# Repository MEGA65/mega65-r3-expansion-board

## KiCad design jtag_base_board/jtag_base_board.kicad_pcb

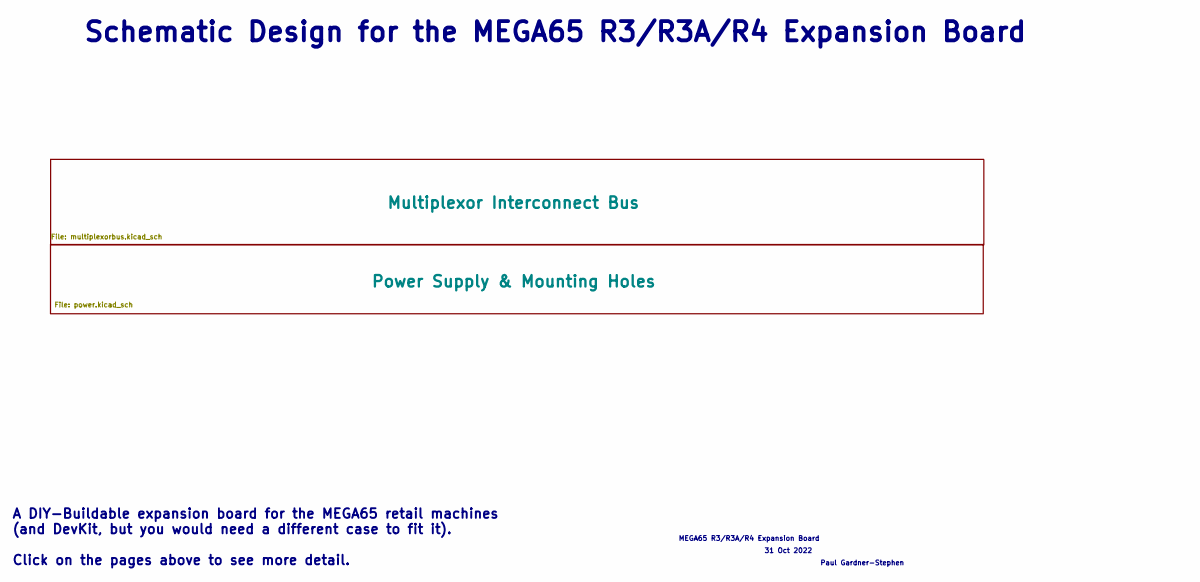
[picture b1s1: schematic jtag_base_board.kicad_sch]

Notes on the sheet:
Paul Gardner-Stephen
A DIY-Buildable expansion board for the MEGA65 retail machines (and DevKit, but you would need a different case to fit it). Click on the pages above to see more detail.
31 Oct 2022
MEGA65 R3/R3A/R4 Expansion Board
Schematic Design for the MEGA65 R3/R3A/R4 Expansion Board

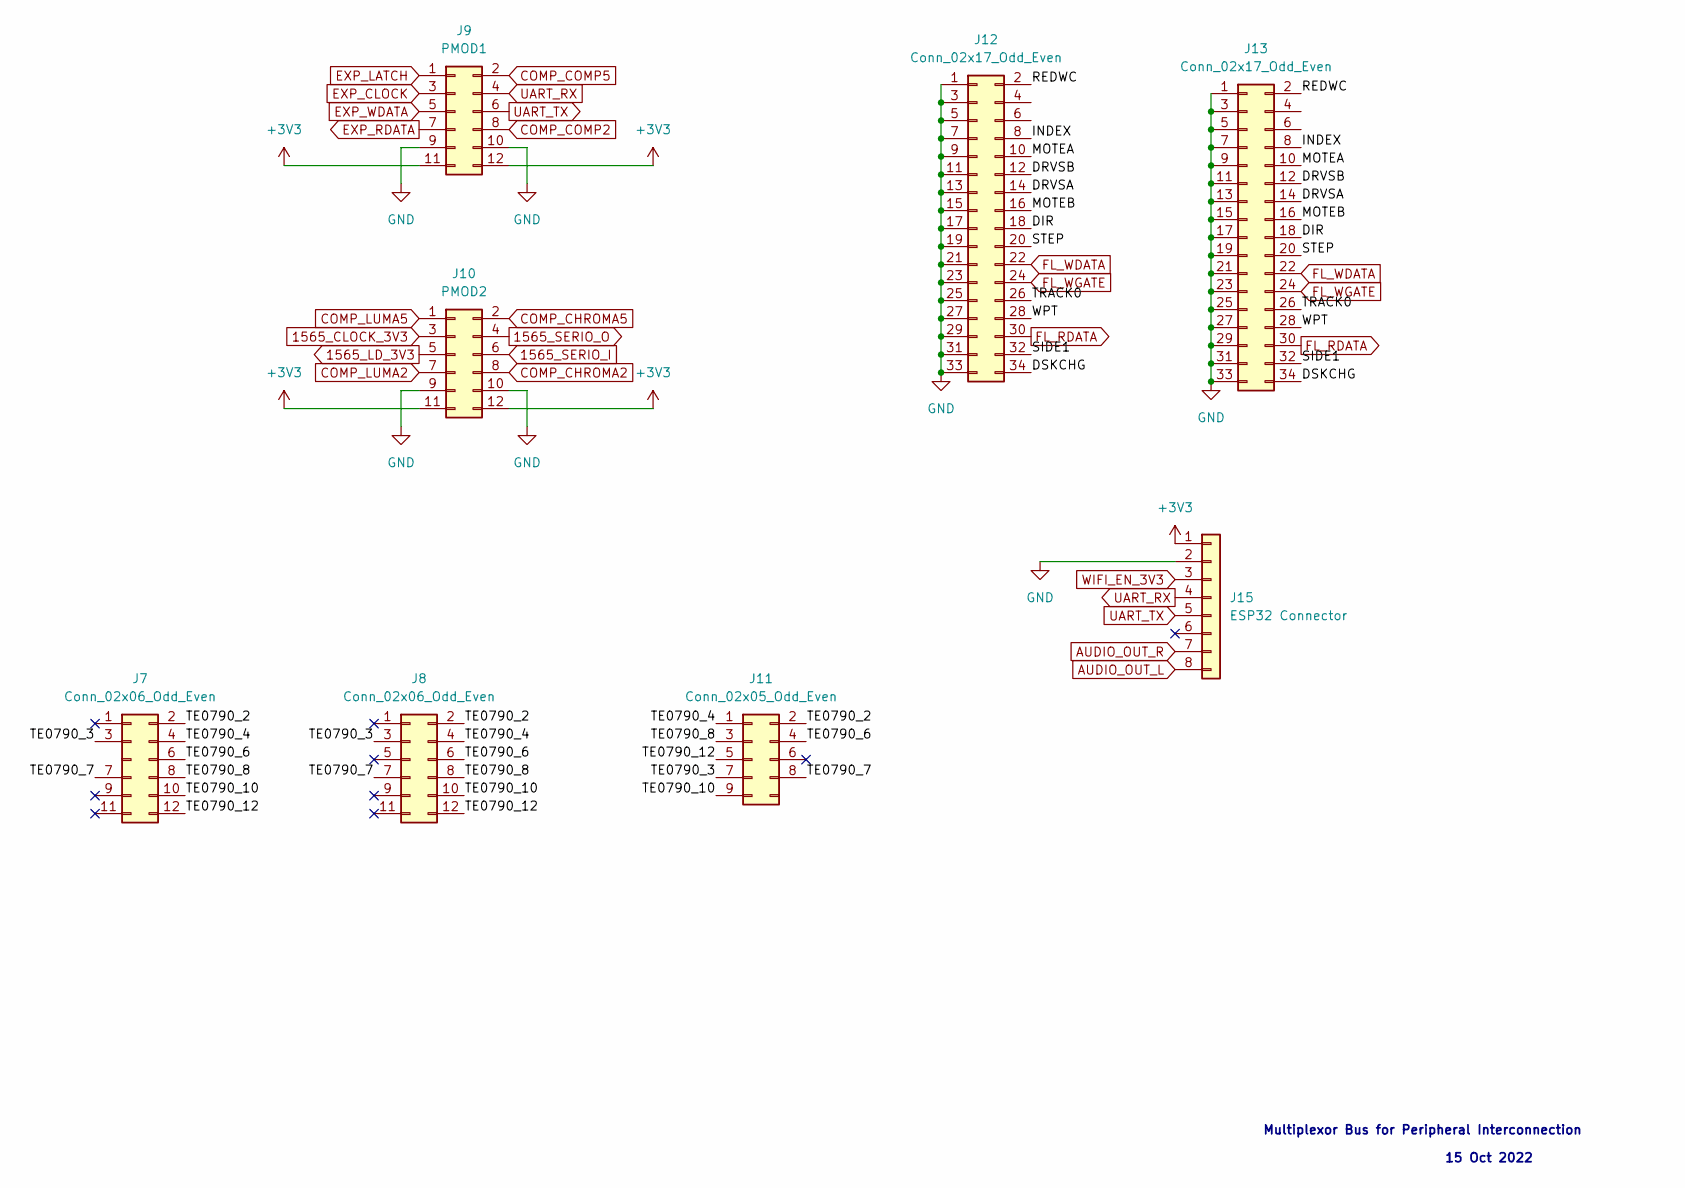
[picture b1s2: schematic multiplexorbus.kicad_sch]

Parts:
J7, J8: Conn_02x06_Odd_Even; PinHeader_2x06_P2.54mm_Vertical
J9: PMOD1; PinHeader_2x06_P2.54mm_Vertical
J10: PMOD2; PinHeader_2x06_P2.54mm_Vertical
J11: Conn_02x05_Odd_Even; PinHeader_2x05_P2.54mm_Vertical
J12, J13: Conn_02x17_Odd_Even; PinHeader_2x17_P2.54mm_Vertical
J15: ESP32 Connector; PinHeader_1x08_P2.54mm_Vertical

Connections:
1565_CLOCK_3V3: J10.3
1565_LD_3V3: J10.5
1565_SERIO_I: J10.6
1565_SERIO_O: J10.4
+3V3: J9.11, J9.12, J10.11, J10.12, J15.1
/Multiplexor Interconnect Bus/DIR: J12.18, J13.18
/Multiplexor Interconnect Bus/DRVSA: J12.14, J13.14
/Multiplexor Interconnect Bus/DRVSB: J12.12, J13.12
/Multiplexor Interconnect Bus/DSKCHG: J12.34, J13.34
/Multiplexor Interconnect Bus/INDEX: J12.8, J13.8
/Multiplexor Interconnect Bus/MOTEA: J12.10, J13.10
/Multiplexor Interconnect Bus/MOTEB: J12.16, J13.16
/Multiplexor Interconnect Bus/REDWC: J12.2, J13.2
/Multiplexor Interconnect Bus/SIDE1: J12.32, J13.32
/Multiplexor Interconnect Bus/STEP: J12.20, J13.20
/Multiplexor Interconnect Bus/TE0790_2: J7.2, J8.2, J11.2
/Multiplexor Interconnect Bus/TE0790_3: J7.3, J8.3, J11.7
/Multiplexor Interconnect Bus/TE0790_4: J7.4, J8.4, J11.1
/Multiplexor Interconnect Bus/TE0790_6: J7.6, J8.6, J11.4
/Multiplexor Interconnect Bus/TE0790_7: J7.7, J8.7, J11.8
/Multiplexor Interconnect Bus/TE0790_8: J7.8, J8.8, J11.3
/Multiplexor Interconnect Bus/TE0790_10: J7.10, J8.10, J11.9
/Multiplexor Interconnect Bus/TE0790_12: J7.12, J8.12, J11.5
/Multiplexor Interconnect Bus/TRACK0: J12.26, J13.26
/Multiplexor Interconnect Bus/WPT: J12.28, J13.28
AUDIO_OUT_L: J15.8
AUDIO_OUT_R: J15.7
COMP_CHROMA2: J10.8
COMP_CHROMA5: J10.2
COMP_COMP2: J9.8
COMP_COMP5: J9.2
COMP_LUMA2: J10.7
COMP_LUMA5: J10.1
EXP_CLOCK: J9.3
EXP_LATCH: J9.1
EXP_RDATA: J9.7
EXP_WDATA: J9.5
FL_RDATA: J12.30, J13.30
FL_WDATA: J12.22, J13.22
FL_WGATE: J12.24, J13.24
GND: J9.9, J9.10, J10.9, J10.10, J12.1, J12.3, J12.5, J12.7, J12.9, J12.11, J12.13, J12.15, J12.17, J12.19, J12.21, J12.23, J12.25, J12.27, J12.29, J12.31, J12.33, J13.1, J13.3, J13.5, J13.7, J13.9, J13.11, J13.13, J13.15, J13.17, J13.19, J13.21, J13.23, J13.25, J13.27, J13.29, J13.31, J13.33, J15.2; also elsewhere on the board
UART_RX: J9.4, J15.4
UART_TX: J9.6, J15.5
WIFI_EN_3V3: J15.3

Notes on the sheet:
Multiplexor Bus for Peripheral Interconnection
15 Oct 2022

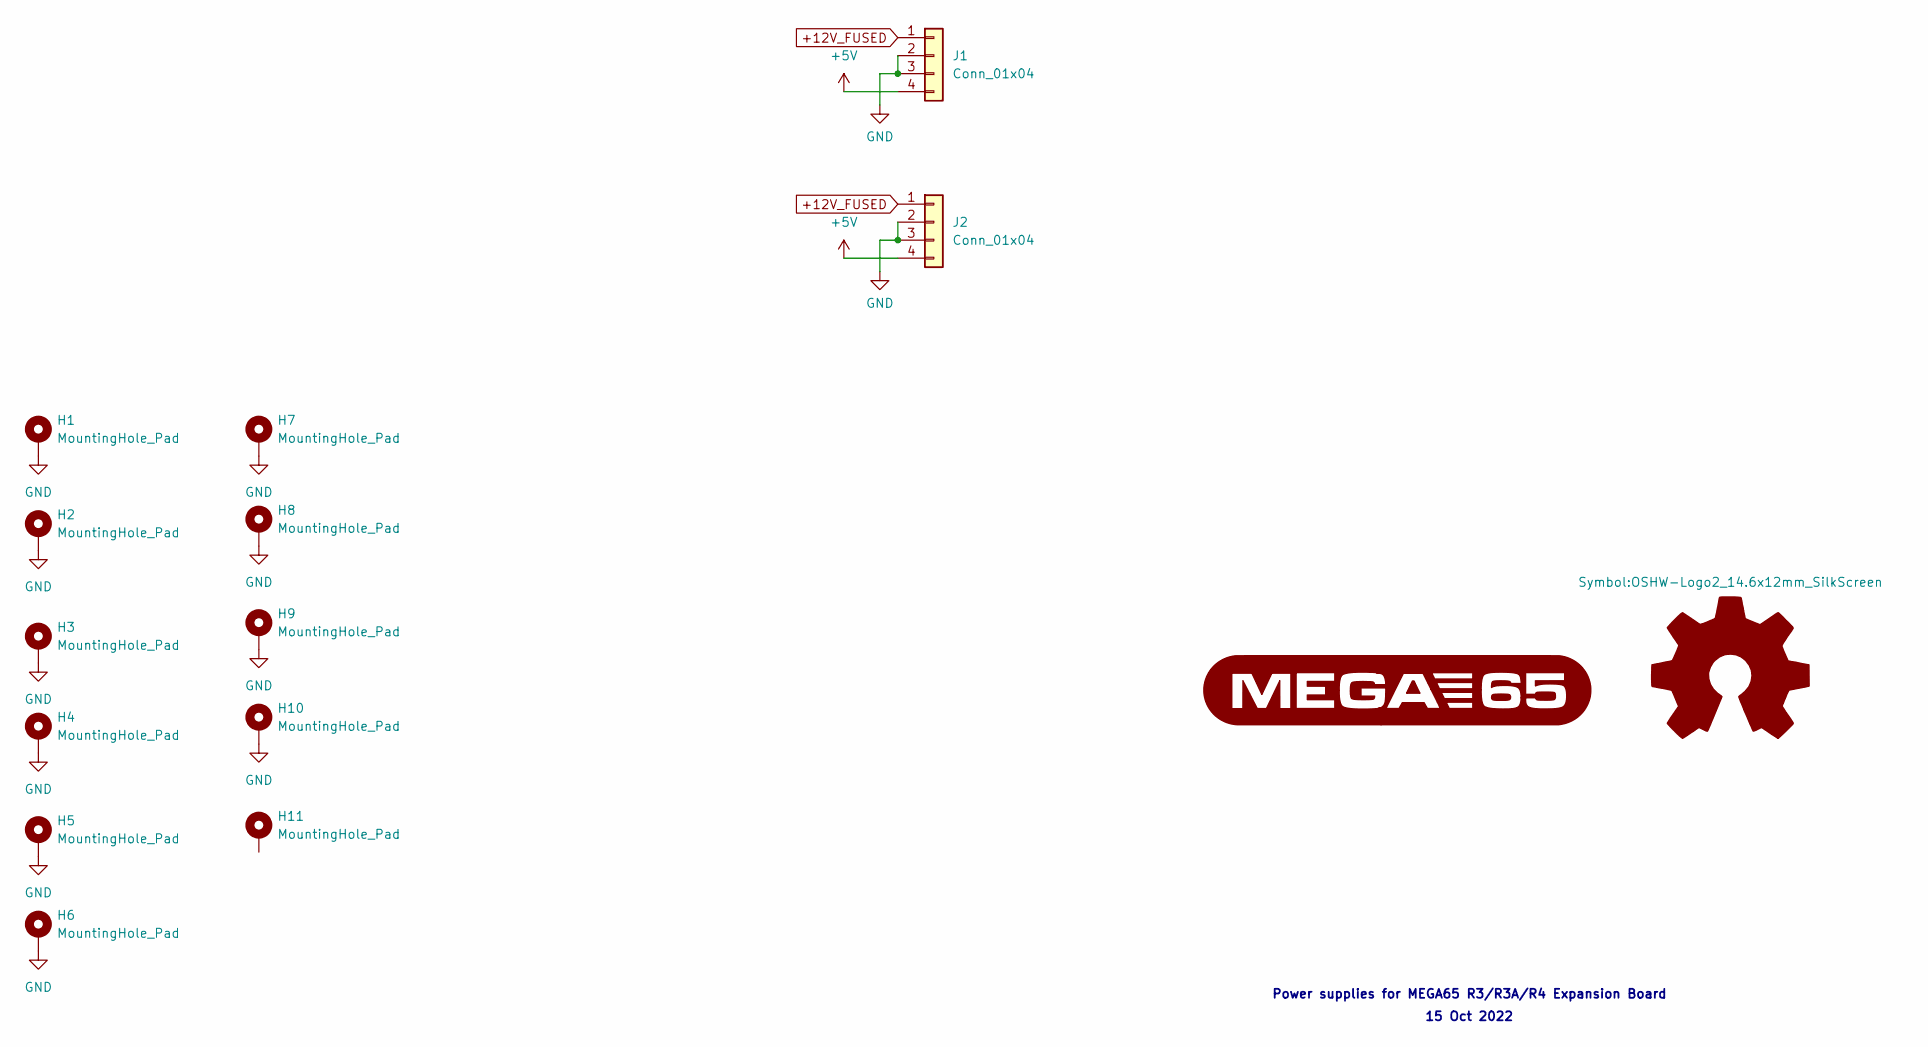
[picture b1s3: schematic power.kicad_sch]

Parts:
H1, H2, H3, H4, H5, H6, H7, H8, H9, H10, H11: MountingHole_Pad; MountingHole_3.2mm_M3_DIN965_Pad
J1, J2: Conn_01x04; FloppyPower
LOGO1: Logo_Open_Hardware_Large; OSHW-Logo2_14.6x12mm_SilkScreen

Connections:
+5V: J1.4, J2.4
+12V_FUSED: J1.1, J2.1
GND: H1.1 (1_1), H2.1 (1_1), H3.1 (1_1), H4.1 (1_1), H5.1 (1_1), H6.1 (1_1), H7.1 (1_1), H8.1 (1_1), H9.1 (1_1), H10.1 (1_1), J1.2, J1.3, J2.2, J2.3; also elsewhere on the board

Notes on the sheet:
Power supplies for MEGA65 R3/R3A/R4 Expansion Board
15 Oct 2022

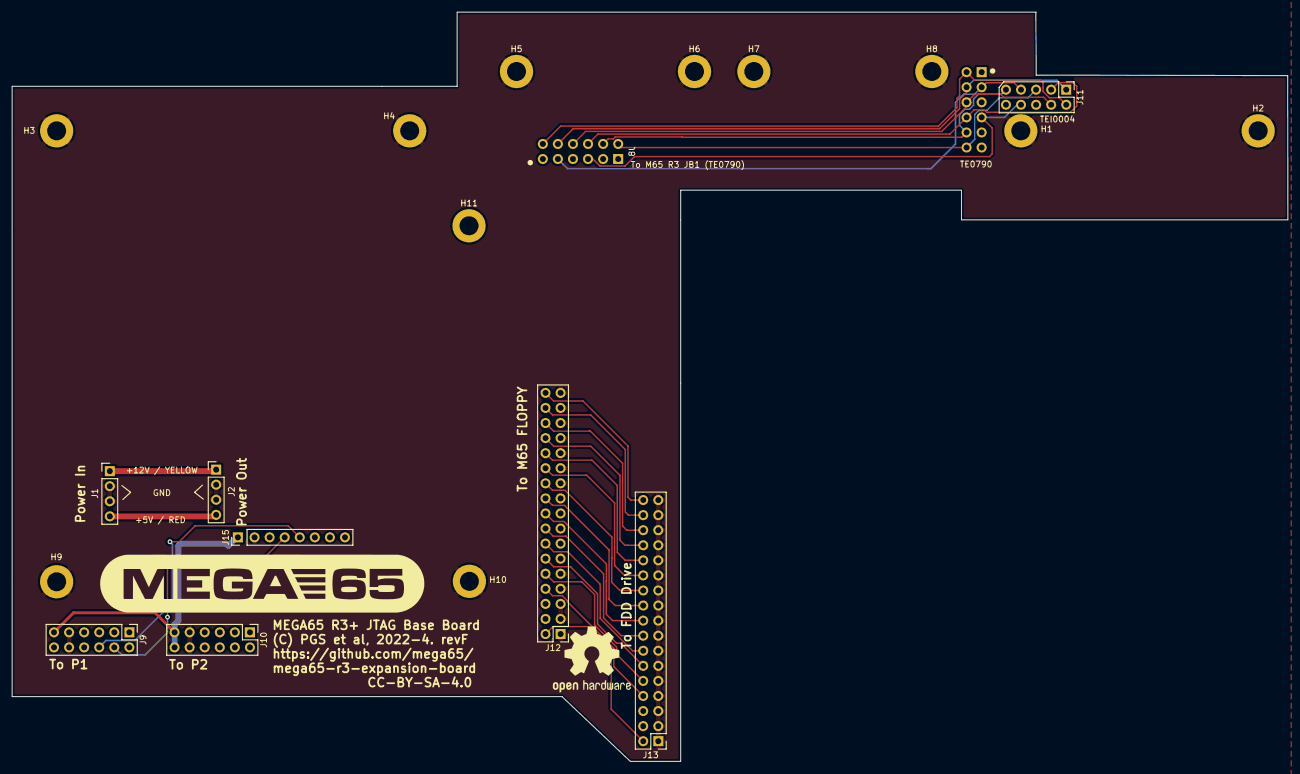
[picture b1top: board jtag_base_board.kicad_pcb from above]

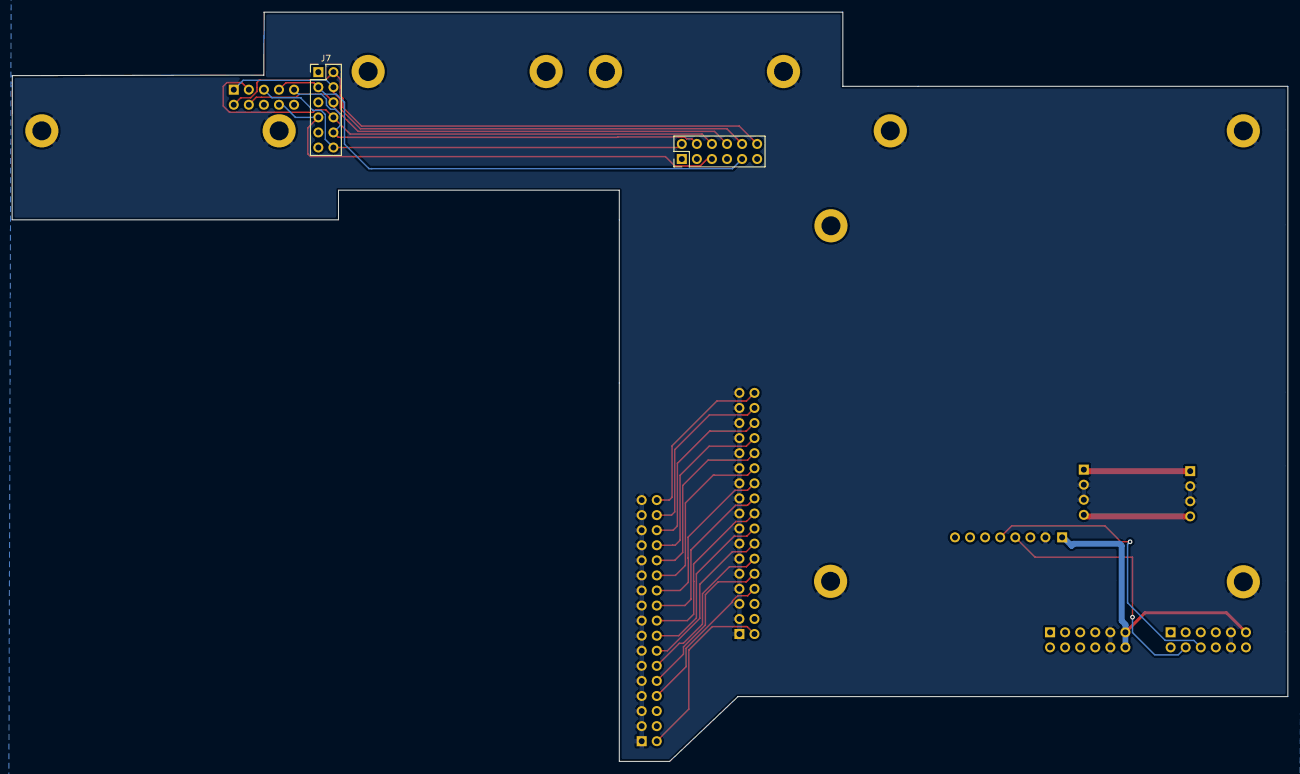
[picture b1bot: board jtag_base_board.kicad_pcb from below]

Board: 2 copper layers, 215.0 x 126.3 mm, 22 parts (2 on the bottom side), 29 nets.

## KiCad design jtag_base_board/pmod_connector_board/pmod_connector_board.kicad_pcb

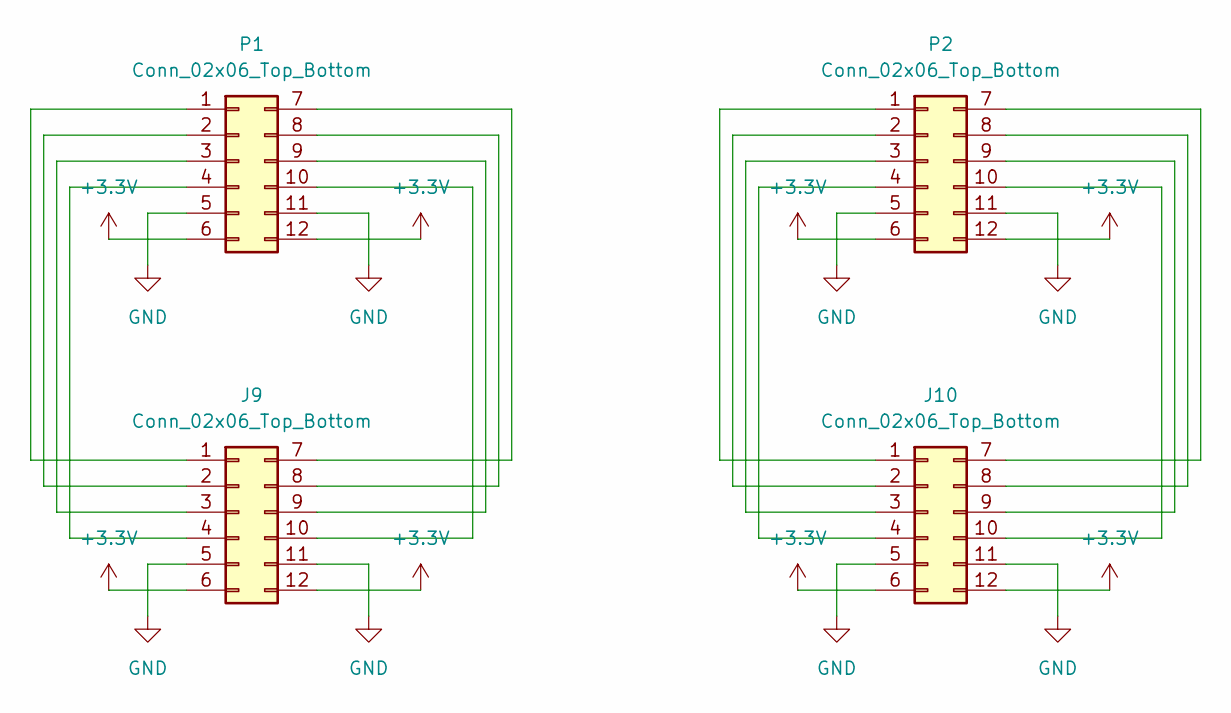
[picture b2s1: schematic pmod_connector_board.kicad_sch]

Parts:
J9, J10: Conn_02x06_Top_Bottom; PinHeader_2x06_P1.00mm_Vertical
P1, P2: Conn_02x06_Top_Bottom; PinHeader_2x06_P1.00mm_Vertical

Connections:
+3V3: J9.6, J9.12, J10.6, J10.12, P1.6, P1.12, P2.6, P2.12
GND: J9.5, J9.11, J10.5, J10.11, P1.5, P1.11, P2.5, P2.11
unnamed: J9.1, P1.1
unnamed: J9.2, P1.2
unnamed: J9.3, P1.3
unnamed: J9.4, P1.4
unnamed: J9.7, P1.7
unnamed: J9.8, P1.8
unnamed: J9.9, P1.9
unnamed: J9.10, P1.10
unnamed: J10.1, P2.1
unnamed: J10.2, P2.2
unnamed: J10.3, P2.3
unnamed: J10.4, P2.4
unnamed: J10.7, P2.7
unnamed: J10.8, P2.8
unnamed: J10.9, P2.9
unnamed: J10.10, P2.10

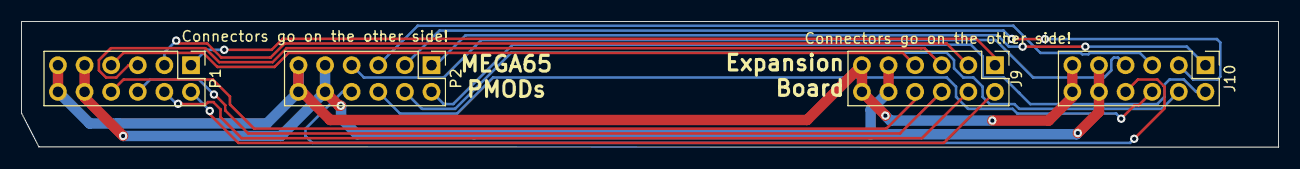
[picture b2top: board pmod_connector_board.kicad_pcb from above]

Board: 2 copper layers, 120.0 x 12.0 mm, 4 parts (0 on the bottom side), 18 nets.

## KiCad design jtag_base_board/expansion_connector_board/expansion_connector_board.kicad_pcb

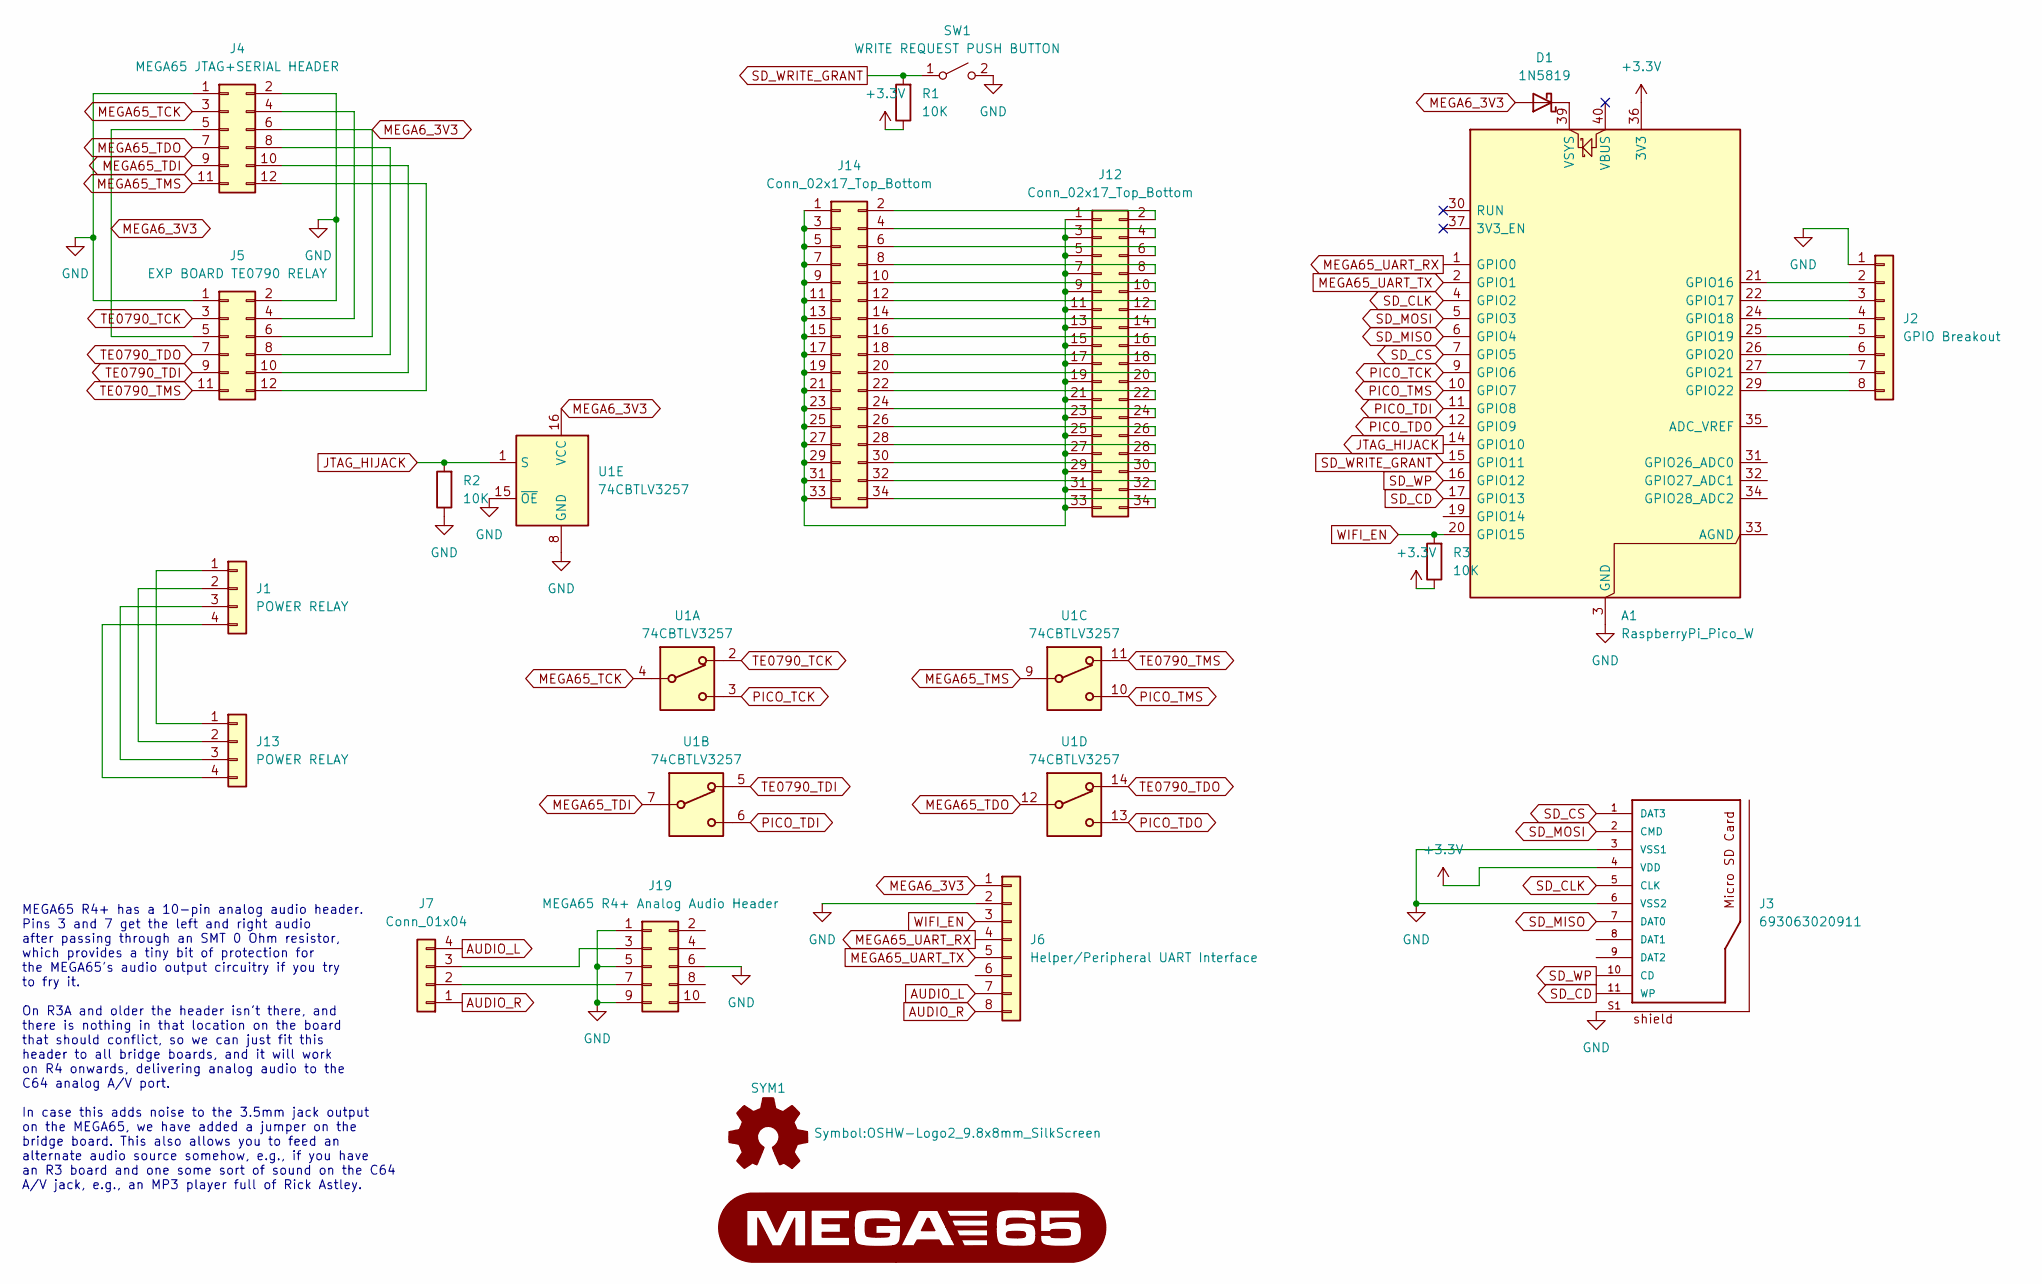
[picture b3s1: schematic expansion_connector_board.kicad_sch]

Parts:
A1: RaspberryPi_Pico_W; RaspberryPi_Pico_W_SMD_HandSolder
D1: 1N5819; D_DO-41_SOD81_P10.16mm_Horizontal
G1: LOGO; MEGA65-logo
J1, J13: POWER RELAY; PinHeader_1x04_P2.54mm_Vertical
J2: GPIO Breakout; PinHeader_1x08_P2.54mm_Vertical
J3: 693063020911
J4: MEGA65 JTAG+SERIAL HEADER; PinHeader_2x06_P2.54mm_Vertical
J5: EXP BOARD TE0790 RELAY; PinHeader_2x06_P2.54mm_Vertical
J6: Helper/Peripheral UART Interface; PinHeader_1x08_P2.54mm_Vertical
J7: Conn_01x04; PinHeader_1x04_P2.54mm_Vertical
J12, J14: Conn_02x17_Top_Bottom; PinHeader_2x17_P2.54mm_Vertical
J19: MEGA65 R4+ Analog Audio Header; PinHeader_2x05_P2.54mm_Vertical
R1, R2, R3: 10K; R_Axial_DIN0207_L6.3mm_D2.5mm_P10.16mm_Horizontal
SW1: WRITE REQUEST PUSH BUTTON; TE_2-1825027-0
SYM1: Logo_Open_Hardware_Small; OSHW-Logo2_9.8x8mm_SilkScreen
U1: 74CBTLV3257; SOIC-16_3.9x9.9mm_P1.27mm

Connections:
+3.3V: A1.36 (3V3), J3.4 (VDD), R1.1, R3.1
AUDIO_L: J6.7, J7.4
AUDIO_R: J6.8, J7.1
GND: A1.3 (GND), A1.8 (GND), A1.13 (GND), A1.18 (GND), A1.23 (GND), A1.28 (GND), A1.38 (GND), J2.1, J3.3 (VSS1), J3.6 (VSS2), J3.S1, J3.S2, J3.S3, J3.S4, J4.1, J4.2, J5.1, J5.2, J6.2, J19.1, J19.5, J19.6, J19.9, R2.1, SW1.2 (B), U1.8 (GND), U1.15 (~OE)
JTAG_HIJACK: A1.14 (GPIO10), R2.2, U1.1 (S)
MEGA6_3V3: D1.2 (A), J4.5, J4.6, J5.5, J5.6, J6.1, U1.16 (VCC)
MEGA65_TCK: J4.3, U1.4
MEGA65_TDI: J4.9, U1.7
MEGA65_TDO: J4.7, U1.12
MEGA65_TMS: J4.11, U1.9
MEGA65_UART_RX: A1.1 (GPIO0), J6.4
MEGA65_UART_TX: A1.2 (GPIO1), J6.5
unnamed: A1.21 (GPIO16), J2.2
unnamed: A1.22 (GPIO17), J2.3
unnamed: A1.24 (GPIO18), J2.4
unnamed: A1.25 (GPIO19), J2.5
unnamed: A1.26 (GPIO20), J2.6
unnamed: A1.27 (GPIO21), J2.7
unnamed: A1.29 (GPIO22), J2.8
unnamed: A1.39 (VSYS), D1.1 (K)
unnamed: J1.1, J13.1
unnamed: J1.2, J13.2
unnamed: J1.3, J13.3
unnamed: J1.4, J13.4
unnamed: J4.4, J5.4
unnamed: J4.8, J5.8
unnamed: J4.10, J5.10
unnamed: J4.12, J5.12
unnamed: J12.1, J12.3, J12.5, J12.7, J12.9, J12.11, J12.13, J12.15, J12.17, J12.19, J12.21, J12.23, J12.25, J12.27, J12.29, J12.31, J12.33, J14.1, J14.3, J14.5, J14.7, J14.9, J14.11, J14.13, J14.15, J14.17, J14.19, J14.21, J14.23, J14.25, J14.27, J14.29, J14.31, J14.33
unnamed: J12.2, J14.2
unnamed: J12.4, J14.4
unnamed: J12.6, J14.6
unnamed: J12.8, J14.8
unnamed: J12.10, J14.10
unnamed: J12.12, J14.12
unnamed: J12.14, J14.14
unnamed: J12.16, J14.16
unnamed: J12.18, J14.18
unnamed: J12.20, J14.20
unnamed: J12.22, J14.22
unnamed: J12.24, J14.24
unnamed: J12.26, J14.26
unnamed: J12.28, J14.28
unnamed: J12.30, J14.30
unnamed: J12.32, J14.32
unnamed: J12.34, J14.34
unnamed: J7.3, J19.3
unnamed: J7.2, J19.7
PICO_TCK: A1.9 (GPIO6), U1.3
PICO_TDI: A1.11 (GPIO8), U1.6
PICO_TDO: A1.12 (GPIO9), U1.13
PICO_TMS: A1.10 (GPIO7), U1.10
SD_CD: A1.17 (GPIO13), J3.11 (WP)
SD_CLK: A1.4 (GPIO2), J3.5 (CLK)
SD_CS: A1.7 (GPIO5), J3.1 (DAT3)
SD_MISO: A1.6 (GPIO4), J3.7 (DAT0)
SD_MOSI: A1.5 (GPIO3), J3.2 (CMD)
SD_WP: A1.16 (GPIO12), J3.10 (CD)
SD_WRITE_GRANT: A1.15 (GPIO11), R1.2, SW1.1 (A)
TE0790_TCK: J5.3, U1.2
TE0790_TDI: J5.9, U1.5
TE0790_TDO: J5.7, U1.14
TE0790_TMS: J5.11, U1.11
WIFI_EN: A1.20 (GPIO15), J6.3, R3.2

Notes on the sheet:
MEGA65 R4+ has a 10-pin analog audio header. Pins 3 and 7 get the left and right audio after passing through an SMT 0 Ohm resistor, which provides a tiny bit of protection for the MEGA65's audio output circuitry if you try to fry it. On R3A and older the header isn't there, and there is nothing in 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

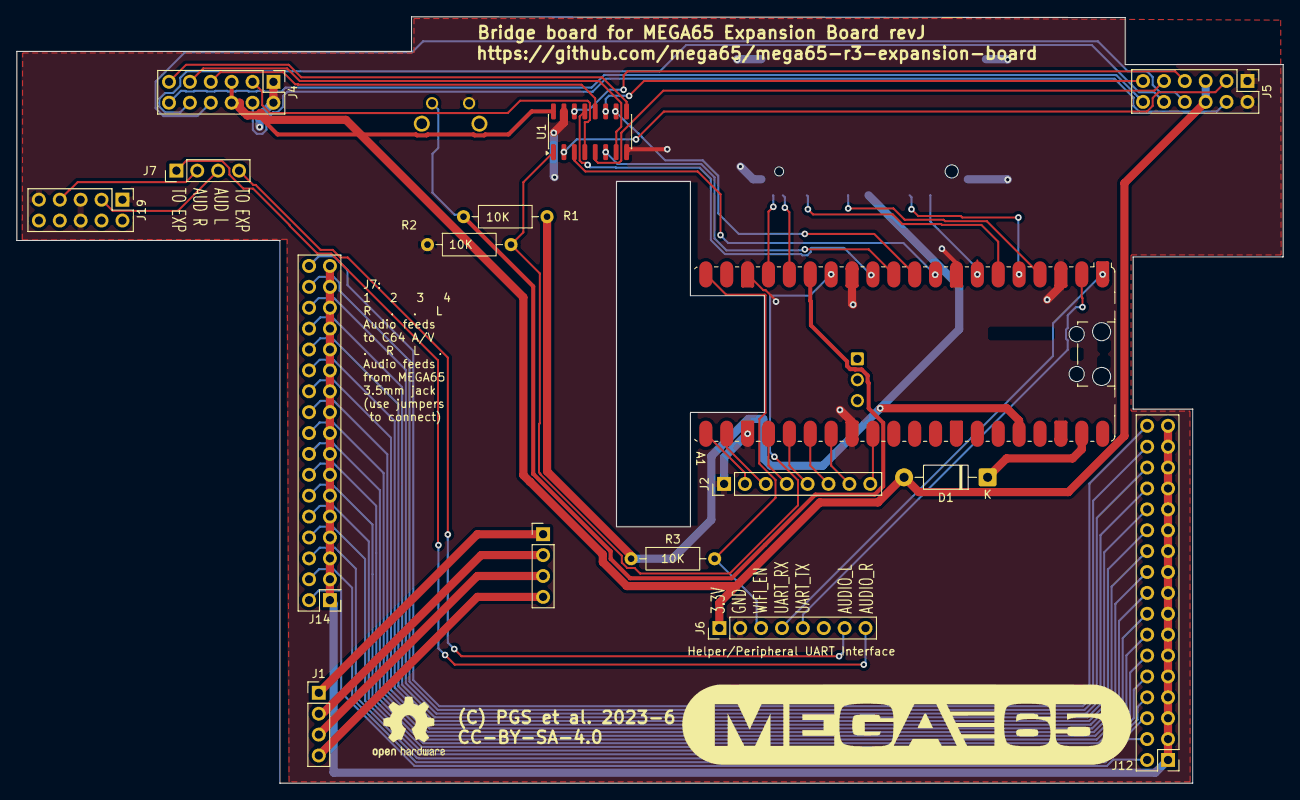
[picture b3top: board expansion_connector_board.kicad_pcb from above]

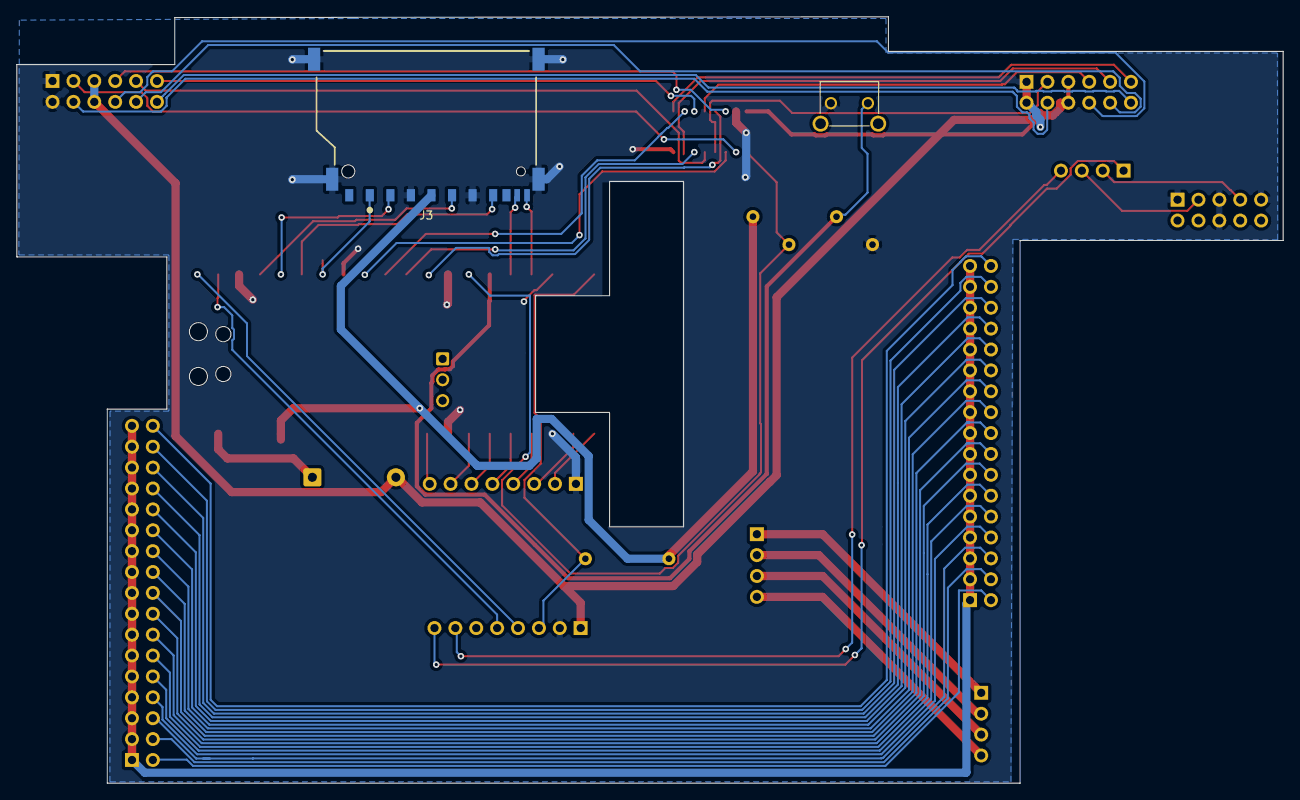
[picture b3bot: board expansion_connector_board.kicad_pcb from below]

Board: 2 copper layers, 154.0 x 93.2 mm, 20 parts (2 on the bottom side), 64 nets.

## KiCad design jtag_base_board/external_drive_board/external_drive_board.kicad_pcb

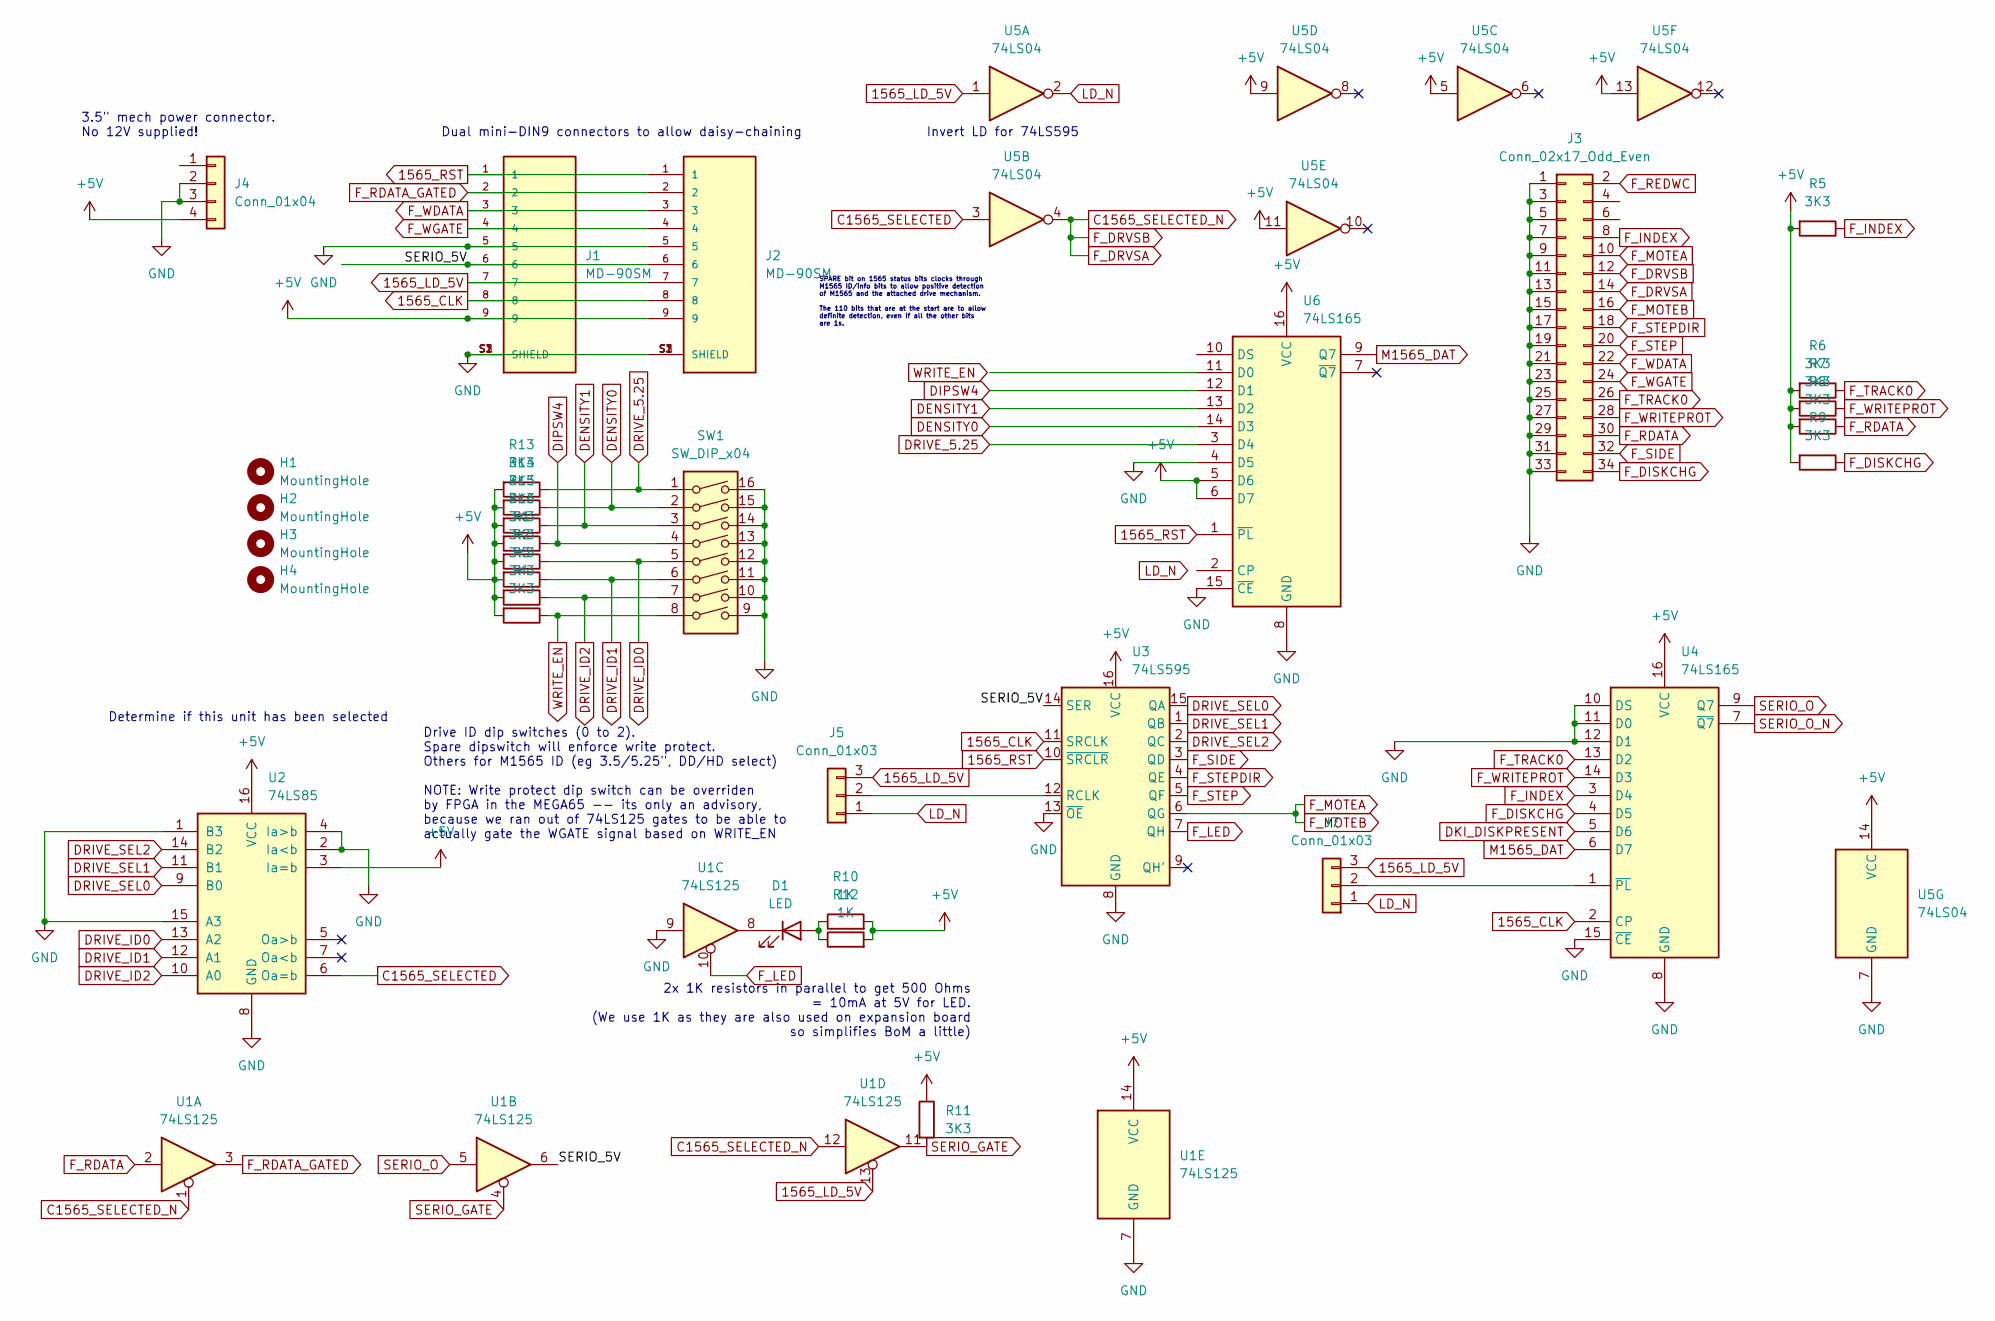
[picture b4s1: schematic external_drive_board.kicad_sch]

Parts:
D1: LED; LED_D5.0mm
H1, H2, H3, H4: MountingHole; MountingHole_3mm_Pad
J1, J2: MD-90SM; CUI_MD-90SM; PARTREV 02/18/2022
J3: Conn_02x17_Odd_Even; PinHeader_2x17_P2.54mm_Vertical
J4: Conn_01x04; PinHeader_1x04_P2.54mm_Vertical
J5, J7: Conn_01x03; PinHeader_1x03_P2.54mm_Vertical
R1, R2, R3, R4, R5, R6, R7, R8, R9, R11, R13, R14, R15, R16: 3K3; R_Axial_DIN0207_L6.3mm_D2.5mm_P7.62mm_Horizontal
R10, R12: 1K; R_Axial_DIN0207_L6.3mm_D2.5mm_P7.62mm_Horizontal
SW1: SW_DIP_x04; DIP-16_W7.62mm
U1: 74LS125; DIP-14_W7.62mm
U2: 74LS85; DIP-16_W7.62mm
U3: 74LS595; DIP-16_W7.62mm
U4, U6: 74LS165; DIP-16_W7.62mm
U5: 74LS04; DIP-14_W7.62mm

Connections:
1565_CLK: J1.8, J2.8, U3.11 (SRCLK), U4.2 (CP)
1565_LD_5V: J1.7, J2.7, J5.3, J7.3, U1.13, U5.1
1565_RST: J1.1, J2.1, U3.10 (~SRCLR), U6.1 (~PL)
+5V: J1.9, J2.9, J4.4, R1.2, R2.2, R3.2, R4.2, R5.2, R6.2, R7.2, R8.2, R9.2, R10.2, R11.1, R12.2, R13.2, R14.2, R15.2, R16.2, U1.14 (VCC), U2.3 (Ia=b), U2.16 (VCC), U3.16 (VCC), U4.16 (VCC), U5.5, U5.9, U5.11, U5.13, U5.14 (VCC), U6.5 (D6), U6.6 (D7), U6.16 (VCC)
/SERIO_5V: J1.6, J2.6, U1.6, U3.14 (SER)
C1565_SELECTED: U2.6 (Oa=b), U5.3
C1565_SELECTED_N: J3.12, J3.14, U1.1, U1.12, U5.4
DENSITY0: R14.1, SW1.2, U6.14 (D3)
DENSITY1: R15.1, SW1.3, U6.13 (D2)
DIPSW4: R16.1, SW1.4, U6.12 (D1)
DKI_DISKPRESENT: U4.5 (D6)
DRIVE_5.25: R13.1, SW1.1, U6.3 (D4)
DRIVE_ID0: R1.1, SW1.5, U2.13 (A2)
DRIVE_ID1: R2.1, SW1.6, U2.12 (A1)
DRIVE_ID2: R3.1, SW1.7, U2.10 (A0)
DRIVE_SEL0: U2.9 (B0), U3.15 (QA)
DRIVE_SEL1: U2.11 (B1), U3.1 (QB)
DRIVE_SEL2: U2.14 (B2), U3.2 (QC)
F_DISKCHG: J3.34, R9.1, U4.4 (D5)
F_INDEX: J3.8, R5.1, U4.3 (D4)
F_LED: U1.10, U3.7 (QH)
F_MOTEA: J3.10, J3.16, U3.6 (QG)
F_RDATA: J3.30, R8.1, U1.2
F_RDATA_GATED: J1.2, J2.2, U1.3
F_REDWC: J3.2
F_SIDE: J3.32, U3.3 (QD)
F_STEP: J3.20, U3.5 (QF)
F_STEPDIR: J3.18, U3.4 (QE)
F_TRACK0: J3.26, R6.1, U4.13 (D2)
F_WDATA: J1.3, J2.3, J3.22
F_WGATE: J1.4, J2.4, J3.24
F_WRITEPROT: J3.28, R7.1, U4.14 (D3)
GND: J1.5, J1.S1 (SHIELD), J1.S2 (SHIELD), J1.S3 (SHIELD), J2.5, J2.S1 (SHIELD), J2.S2 (SHIELD), J2.S3 (SHIELD), J3.1, J3.3, J3.5, J3.7, J3.9, J3.11, J3.13, J3.15, J3.17, J3.19, J3.21, J3.23, J3.25, J3.27, J3.29, J3.31, J3.33, J4.2, J4.3, SW1.9, SW1.10, SW1.11, SW1.12, SW1.13, SW1.14, SW1.15, SW1.16, U1.7 (GND), U1.9, U2.1 (B3), U2.2 (Ia<b), U2.4 (Ia>b), U2.8 (GND), U2.15 (A3), U3.8 (GND), U3.13 (~OE), U4.8 (GND), U4.10 (DS), U4.11 (D0), U4.12 (D1), U4.15 (~CE), U5.7 (GND), U6.4 (D5), U6.8 (GND), U6.15 (~CE)
LD_N: J5.1, J7.1, U5.2
M1565_DAT: U4.6 (D7), U6.9 (Q7)
unnamed: D1.2 (A), R10.1, R12.1
unnamed: D1.1 (K), U1.8
unnamed: J5.2, U3.12 (RCLK)
unnamed: J7.2, U4.1 (~PL)
SERIO_GATE: R11.2, U1.4, U1.11
SERIO_O: U1.5, U4.9 (Q7)
SERIO_O_N: U4.7 (~Q7)
WRITE_EN: R4.1, SW1.8

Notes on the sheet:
SPARE bit on 1565 status bits clocks through M1565 ID/info bits to allow positive detection of M1565 and the attached drive mechanism. The 110 bits that are at the start are to allow definite detection, even if all the other bits are 1s.
Invert LD for 74LS595
Determine if this unit has been selected
2x 1K resistors in parallel to get 500 Ohms = 10mA at 5V for LED. (We use 1K as they are also used on expansion board so simplifies BoM a little)
Dual mini-DIN9 connectors to allow daisy-chaining
Drive ID dip switches (0 to 2). Spare dipswitch will enforce write protect. Others for M1565 ID (eg 3.5/5.25", DD/HD select) NOTE: Write protect dip switch can be overriden by FPGA in the MEGA65 -- its only an advisory, because we ran out of 74LS125 gates to be able to actually gate the WGATE signa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
3.5" mech power connector. No 12V supplied!

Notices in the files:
jtag_base_board/expansion_connector_board/expansion_connector_board.kicad_pcb:
CC-BY-SA-4.0
jtag_base_board/pmod_connector_board/pmod_connector_board.kicad_pcb:
(C) Paul Gardner-Stephen 2024, CC-BY 4.0
